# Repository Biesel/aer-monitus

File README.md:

# **Título del Proyecto:** Sistema de Monitoreo de Calidad del Aire y Temperatura con ESP32 AER MONITUS

**Descripción del Proyecto:**

El proyecto de "Sistema de Monitoreo de Calidad del Aire y Temperatura con ESP32 AER MONITUS" tiene como objetivo principal crear un dispositivo para monitorear la calidad del aire y la temperatura en entornos internos. Utilizando sensores de CO2 y temperatura, este sistema proporcionará mediciones en tiempo real para garantizar un ambiente interior seguro y cómodo.

**Características Principales:**

1. **Sensores:** El sistema está equipado con sensores para medir los niveles de dióxido de carbono (CO2) y la temperatura en el entorno.

2. **Plataforma ESP32:** Se utiliza el microcontrolador ESP32 por su eficiencia energética y capacidades de conectividad, lo que permite una recopilación de datos precisa y confiable.

3. **Conectividad Inalámbrica:** El dispositivo se conecta a través de Wi-Fi, permitiendo la transmisión instantánea de datos.

4. **Notificaciones en Tiempo Real:** Cuando se detecta una mala calidad del aire o temperaturas altas, el sistema enviará notificaciones inmediatas a los dispositivos móviles de los usuarios a través de mensajes de texto o aplicaciones de mensajería.

5. **Alertas Personalizadas:** Los usuarios pueden configurar umbrales personalizados para las lecturas de CO2 y temperatura, recibiendo alertas específicas cuando los valores superan estos límites.

6. **Diseño Compacto y Portátil:** El dispositivo cuenta con un diseño compacto que se puede colocar en cualquier lugar del entorno interior sin ocupar mucho espacio.

**Beneficios del Proyecto:**

1. **Salud y Seguridad:** Proporciona un ambiente interior seguro y saludable al alertar a los ocupantes sobre niveles peligrosos de CO2 o temperaturas extremas.

2. **Conciencia Ambiental:** Fomenta la conciencia sobre la calidad del aire interior y su impacto en la salud y el bienestar de las personas.

El proyecto del "Sistema de Monitoreo de Calidad del Aire y Temperatura con ESP32 AER MONITUS" representa una solución práctica para mejorar la calidad de vida en entornos internos, proporcionando a los usuarios información en tiempo real para tomar decisiones informadas sobre su salud y seguridad.

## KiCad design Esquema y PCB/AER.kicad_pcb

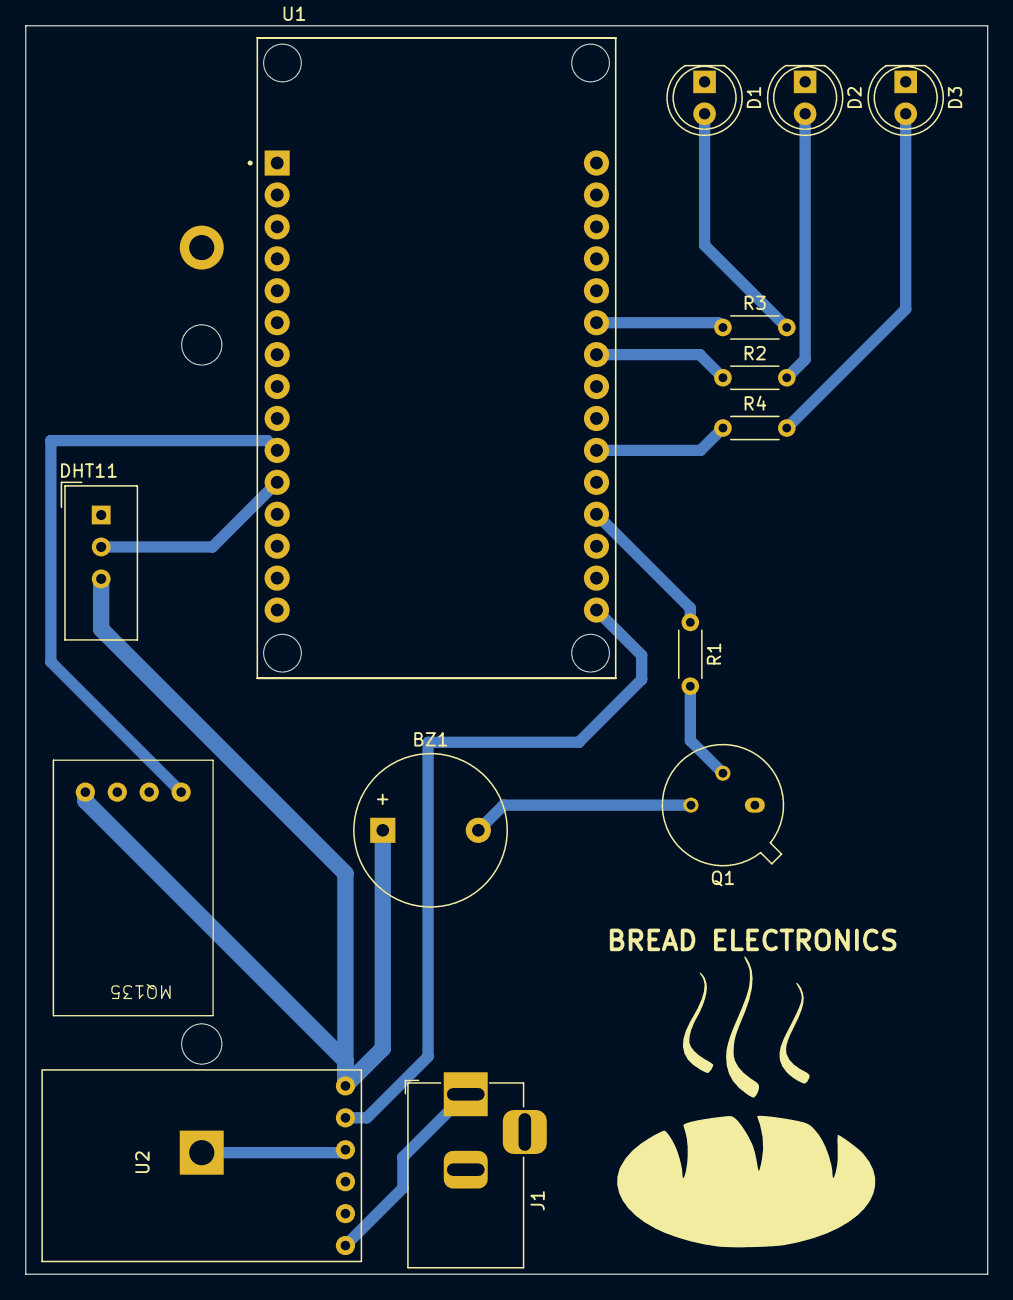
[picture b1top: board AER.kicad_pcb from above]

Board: 2 copper layers, 76.5 x 99.3 mm, 16 parts (1 on the bottom side), 16 nets.

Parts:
BREAD ELECTRONICS: LOGO; bread_logo
BT1: Battery; BatteryHolder_MPD_BH-18650-PC2
BZ1: Buzzer; Buzzer_12x9.5RM7.6
D1, D2, D3: LED; LED_D5.0mm
DHT11: Aosong_DHT11_5.5x12.0_P2.54mm
J1: Jack-DC; BarrelJack_Horizontal
MQ135: MQ135
Q1: 2N2219; TO-39-3
R1, R2, R3, R4: R; R_Axial_DIN0204_L3.6mm_D1.6mm_P5.08mm_Horizontal
U1: ESP32-DEVKIT-V1; MODULE_ESP32_DEVKIT_V1
U2: MH-CD42; mh-cd42

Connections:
+5V: BZ1.1 (-), DHT11.3 (VCC), MQ135.4 (VCC), U2.6 (OUT-5V)
D19: MQ135.1 (A0), U1.10 (D19)
D21: DHT11.2 (DAT), U1.11 (D21)
GND: BT1.2 (-), D1.1 (K), D2.1 (K), D3.1 (K), DHT11.1 (GND), J1.2, MQ135.3 (GND), Q1.1 (E), U1.2 (GND), U1.29 (GND), U2.2 (GND), U2.3 (GND)
unnamed: BT1.1 (+), U2.4 (BAT)
unnamed: BZ1.2 (+), Q1.3 (C)
unnamed: D2.2 (A), R2.2
unnamed: D1.2 (A), R3.2
unnamed: D3.2 (A), R4.2
unnamed: Q1.2 (B), R1.2
unnamed: R2.1, U1.24 (D26)
unnamed: R3.1, U1.25 (D27)
unnamed: R4.1, U1.21 (D32)
unnamed: R1.1, U1.19 (D34)
unnamed: U1.16 (EN), U2.5 (GND)
unnamed: J1.1, U2.1 (VIN)

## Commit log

2023-10-04 Update README.md for description of project
2023-11-15 Added structure, code, 3d models, schematic and pcb designs
2023-11-22 Added new structure and files to AER
2023-11-22 Added image to Laser Cut and .ino code
